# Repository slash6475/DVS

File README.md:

# DVS: Electronic Devil Stick
This project is an introduction to how to build quickly a native IP-based connected object on tiny platform. 
DVS is a simple electronic board composed of a 8 bits- microcontroller with Zigbee tranceiver, an accelerometer and some leds on child boards with an external button.
The software is implemented on Contiki OS, this micro-kernel dedicated to the Internet Of Thing allows 6LoWPAN networking (uIP stack with RPL for mesh network routing),
file system management to store data on flash or eeprom memories, shell interface over serial line, embedded webserver and more.

A simple Javascript page allows to design programs of RGB led sequences and to load them on the DVS platform over HTTP.
The programs are stored into the DVS file system and play on the leds according to the selected program by the external button.
In addition, the accelerometer and wireless communication can be used to control the leds. 
The wireless communication based on 6LoWPAN and HTTP can be operated by any other DVS platforms or computers.
Based on these features, a lot of scenarios and applications can be imagined. 

# Software
Contiki OS has a software architecture which facilitates the encapsulation of drivers and applications into independent containers.
Hence each component of DVS software is independent which facilitates implementation, modularity and code re-use.
Thanks to the shell over the serial line, it is possible to test the drivers of RGB leds and accelerometers, to manage the Webserver (start/stop) and the file system formating such as presented in following video.

## Shell Interface
Open the serial line over USB interface: 
```
minicom -D /dev/ttyUSB0 -b 19200
```
At booting time, different information on Contiki OS and DVS software configurations are provided such as networking, boot sequence, etc.
The command help provides the list of available commands:
```
neopixel test
neopixel ID_led R G B
mpu6050 start | stop
...
help
ps
kill
killall

```
## Programming
The software is implemented in C language and cross-platforms (MSP, AVR, ARM, X86, PIC, etc). The compilation must be executed in main project folder.
```
cd contiki-2.6/examples/dvs_main/
```
### Compilation
```
make all TARGET=avr-atmega128rfa1
avr-size --mcu=atmega128rfa1 dvs-main.avr-atmega128rfa1  -C
```

### Preparation
It is preferred to remove fuse and eeprom section to avoid to break fuse configuration and to erase programs stored in memories.
```
avr-objcopy -O ihex -R .eeprom -R .fuse -R .signature dvs-main.avr-atmega128rfa1 dvs-main.hex
```

### Loading
Example to load the program over ISP connector with a JTAG2 device.
```
sudo avrdude -p atmega128rfa1 -c jtag2isp -P usb -Uflash:w:dvs-main.hex
```
### 

## Arduino encapsulation
The DVS uses the accelerometer MPU6050 and the RGB leds Neopixel which have their librairy implemented in Arduino C++. 
Intead of implementing new librairies for Contiki OS, it is possible to link them dynamically at compilation step. 
Build a dvs.ino file with Arduino style and compile it, then remove the main.o and encapsulate it in a dynamic library.
More details in (contiki-2.6/apps/dvs)
```
avr-ar -cvq dvs_arduino.a *.o
```

In DVS Makefile of Contiki:
```
PROJECT_LIBRARIES=../../apps/dvs/libs/dvs_arduino.a
```

# Web Apps
The Web Interface is a simple javascript page which allows to generate and sequence chunk such as presented below. 
The number of program is not limited, however the sum of all sequences of all programs should be lower than file system size (4Kb).
Programs can be deleted individually, a long pressure on external button (> 20s) formats the file system.
```
OPERATION:TIME:RR1GG1BB1RR2GG2BB2 ...
add:0:001000000000000000000000ff0000ff0000000000000000000000000000000000000000ff0000ff0000000000000000000000
```

# Hardware

The master boards is composed of AVR Atmega128rfa1 with IEEE 802.15.4 radio transceiver, an accelerometer MPU6050 an an FTDI chipset for USB serial line. The external connectors provides pins to control Neopixel leds (16 in default child boards) and power stage of 4 AAAA batteries with their charger circuit based on LM317.
More detail and Eagle files in (/hardware).

## Scheme and PCB of Master Board

## Results

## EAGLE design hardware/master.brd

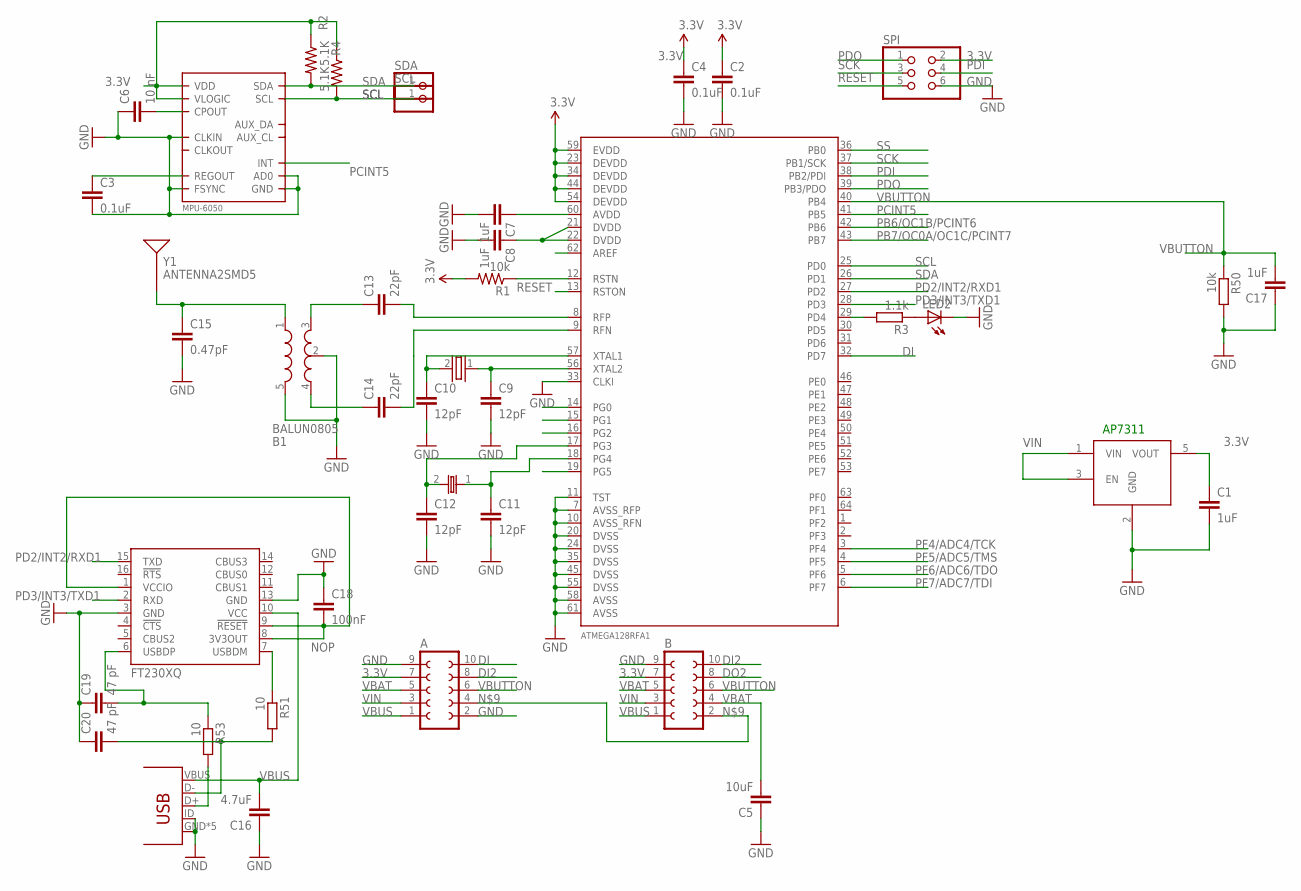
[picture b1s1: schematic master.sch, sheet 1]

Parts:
A: FE05-2W
B: FE05-2W
B1: BALUN0805; BALUN
C1: 1uF; C0603
C2, C3, C4: 0.1uF; 0603-CAP
C5: 10uF; 0603-CAP
C6: 10 nF; 0603-CAP
C7, C8, C17: 1uF; 0805
C9, C10, C11, C12: 12pF; 0603-CAP
C13, C14: 22pF; 0603-CAP
C15: 0.47pF; 0603-CAP
C16: 4.7uF; 0603-CAP
C18: 100nF; 0603-CAP
C19, C20: 47 pF; 0603-CAP
IC1: FT230XQ; QFN16
LED2: LEDCHIPLED_0603; CHIPLED_0603
MICRO-USB: USB-CONNECTOR; MICRO-USB-435-645
QUARTZ1: 753-7203
QUARTZ2: QUARTZ32768
R1: 10k; 0603-RES
R2, R4: 5.1K; 0603-RES
R3: 1.1k; R0603
R50: 10k; R0603
R51, R53: 10; R0603
SCL: PINHD-1X1; 1X01
SDA: PINHD-1X1; 1X01
SPI: PINHD-2X3; 2X03
U1: ATMEGA128RFA1; QFN-64
U$1: MPU-6050; QFN.24.4X4
U$7: MIC5366-2.8YMT; SOT23-5
Y1: ANTENNA2SMD5; ANTENNA-CHIP5

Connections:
3.3V: A.7, B.7, C1.1, C2.1, C4.1, R1.2, R2.1, R4.1, SPI.2, U1.23 (DEVDD), U1.34 (DEVDD), U1.44 (DEVDD), U1.54 (DEVDD), U1.59 (EVDD), U$1.8 (VLOGIC), U$1.13 (VDD), U$7.5 (VOUT)
AREF: U1.62 (AREF)
DI: A.10, U1.32 (PD7)
DI2: A.8, B.10
DO2: B.8
GND: A.2, A.9, B.9, B1.2 (GND), B1.5 (GND), C1.2, C2.2, C3.2, C4.2, C5.1, C6.1, C7.2, C8.2, C9.2, C10.2, C11.2, C12.2, C15.2, C16.1, C17.1, C18.1, C19.1, C20.1, IC1.3 (GND), IC1.13 (GND), LED2.C, MICRO-USB.GND, MICRO-USB.GND1 (GND), MICRO-USB.GND2 (GND), MICRO-USB.GND3 (GND), MICRO-USB.GND4 (GND), MICRO-USB.ID, R50.2, SPI.6, U1.7 (AVSS_RFP), U1.10 (AVSS_RFN), U1.11 (TST), U1.20 (DVSS), U1.24 (DVSS), U1.33 (CLKI), U1.35 (DVSS), U1.45 (DVSS), U1.55 (DVSS), U1.58 (AVSS), U1.61 (AVSS), U$1.1 (CLKIN), U$1.9 (AD0), U$1.11 (FSYNC), U$1.18 (GND), U$7.2 (GND)
unnamed: B1.3 (OUT1), C13.1
unnamed: B1.4 (OUT2), C14.1
unnamed: LED2.A, R3.1
unnamed: B1.1 (IN), C15.1, Y1.FEED
unnamed: C8.1, U1.21 (DVDD), U1.22 (DVDD)
unnamed: C14.2, U1.9 (RFN)
unnamed: C13.2, U1.8 (RFP)
unnamed: R3.2, U1.29 (PD4)
unnamed: A.4, B.2
unnamed: C7.1, U1.60 (AVDD)
unnamed: C3.1, U$1.10 (REGOUT)
unnamed: C10.1, QUARTZ1.2, U1.57 (XTAL1)
unnamed: C9.1, QUARTZ1.1, U1.56 (XTAL2)
unnamed: C12.1, QUARTZ2.2, U1.17 (PG3)
unnamed: C11.1, QUARTZ2.1, U1.18 (PG4)
unnamed: C6.2, U$1.20 (CPOUT)
unnamed: IC1.7 (USBDM), R51.1
unnamed: C20.2, MICRO-USB.D-, R51.2
unnamed: C19.2, IC1.6 (USBDP), R53.1
unnamed: MICRO-USB.D+, R53.2
NOP: C18.2, IC1.1 (VCCIO), IC1.8 (3V3OUT), IC1.9 (!RESET)
PB6/OC1B/PCINT6: U1.42 (PB6)
PB7/OC0A/OC1C/PCINT7: U1.43 (PB7)
PCINT5: U1.41 (PB5), U$1.12 (INT)
PD2/INT2/RXD1: IC1.15 (TXD), U1.27 (PD2)
PD3/INT3/TXD1: IC1.2 (RXD), U1.28 (PD3)
PDI: SPI.4, U1.38 (PB2/PDI)
PDO: SPI.1, U1.39 (PB3/PDO)
PF4/ADC4/TCK: U1.3 (PF4)
PF5/ADC5/TMS: U1.4 (PF5)
PF6/ADC6/TDO: U1.5 (PF6)
PF7/ADC7/TDI: U1.6 (PF7)
PG0: U1.14 (PG0)
PG1: U1.15 (PG1)
PG2: U1.16 (PG2)
PG5: U1.19 (PG5)
RESET: R1.1, SPI.5, U1.12 (RSTN)
RSTON: U1.13 (RSTON)
SCK: SPI.3, U1.37 (PB1/SCK)
SCL: R4.2, SCL.1, U1.25 (PD0), U$1.23 (SCL)
SDA: R2.2, SDA.1, U1.26 (PD1), U$1.24 (SDA)
SS: U1.36 (PB0)
VBAT: A.5, B.4, B.5, C5.2
VBUS: A.1, B.1, C16.2, IC1.10 (VCC), MICRO-USB.VBUS
VBUTTON: A.6, B.6, C17.2, R50.1, U1.40 (PB4)
VIN: A.3, B.3, U$7.1 (VIN), U$7.3 (EN)

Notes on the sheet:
AP7311

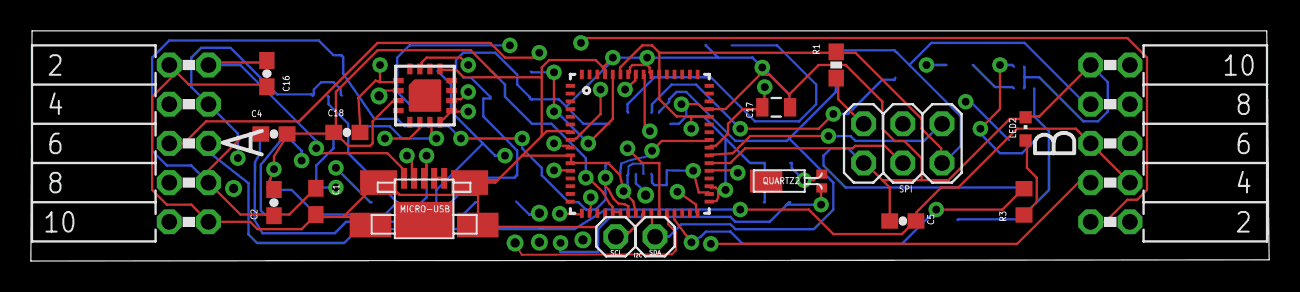
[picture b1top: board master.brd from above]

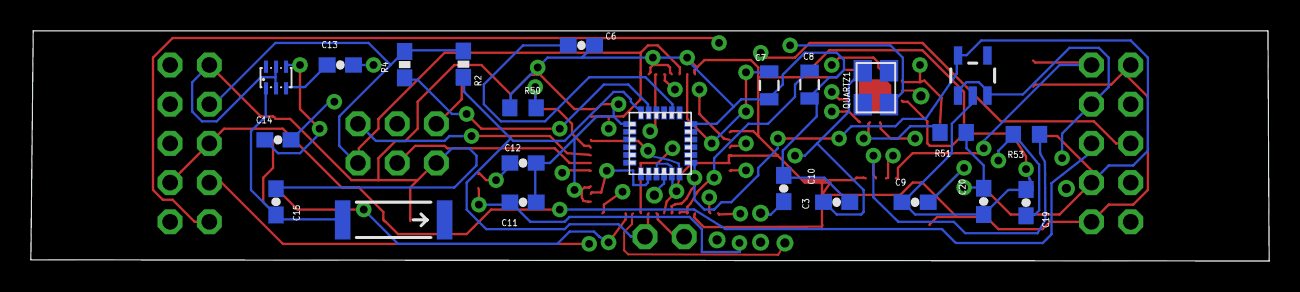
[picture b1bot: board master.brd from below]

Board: 4 copper layers, 80.2 x 14.9 mm, 42 parts (23 on the bottom side), 38 nets.

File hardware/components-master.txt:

Partlist

Exported from BatonDuDiable.brd at 02/02/2016 17:00:12

EAGLE Version 7.4.0 Copyright (c) 1988-2015 CadSoft

Assembly variant: 

Part      Value          Package           Library     Position (inch)       Orientation

A                        FE05-2W           con-lsta    (0.4 1.35)            R270
B                        FE05-2W           con-lsta    (2.75 1.35)           R90
B1        BALUN0805      BALUN             SparkFun    (2.45 1.5)            MR0
C1        1uF            C0603             rcl         (0.7 1.15)            R0
C2        0.1uF          0603-CAP          SparkFun    (0.7 1.25)            R0
C3        0.1uF          0603-CAP          SparkFun    (1.252 1.294)         MR90
C4        0.1uF          0603-CAP          SparkFun    (0.65 1.35)           R0
C5        10uF           0603-CAP          SparkFun    (1.95 1.25)           R270
C6        10 nF          0603-CAP          SparkFun    (1.672 1.575)         MR180
C7        1uF            0805              SparkFun    (1.25 1.5)            MR270
C8        1uF            0805              SparkFun    (1.15 1.5)            MR270
C9        12pF           0603-CAP          SparkFun    (0.9 1.2)             MR180
C10       12pF           0603-CAP          SparkFun    (1.1 1.2)             MR0
C11       12pF           0603-CAP          SparkFun    (1.9 1.2)             MR0
C12       12pF           0603-CAP          SparkFun    (1.9 1.3)             MR0
C13       22pF           0603-CAP          SparkFun    (2.3 1.5)             MR0
C14       22pF           0603-CAP          SparkFun    (2.45 1.35)           MR0
C15       0.47pF         0603-CAP          SparkFun    (2.45 1.2)            MR90
C16       4.7uF          0603-CAP          SparkFun    (0.85 1.5)            R90
C17       1uF            0805              SparkFun    (1.85 1.25)           R90
C18       0.1uF          0603-CAP          SparkFun    (0.8 1.35)            R0
C19       47 pF          0603-CAP          SparkFun    (0.7 1.25)            MR180
C20       47 pF          0603-CAP          SparkFun    (0.7 1.15)            MR180
IC1       FT230XQ        QFN16             ftdichip    (1 1.45)              R0
LED2                     CHIPLED_0603      led         (2.45 1.4)            R0
MICRO-USB USB-CONNECTOR  MICRO-USB-435-645 myrobotics2 (1 1.25)              R0
QUARTZ1   753-7203       753-7203          myrobotics2 (1 1.45)              MR90
QUARTZ2   QUARTZ32768    QUARTZ32768       myrobotics2 (1.9 1.4)             MR270
R1        10k            0603-RES          SparkFun    (2.05 1.5)            R180
R2        5.1K           0603-RES          SparkFun    (2.05 1.5)            MR270
R3        1.1k           R0603             rcl         (2.45 1.25)           R90
R4        5.1K           0603-RES          SparkFun    (2.15 1.5)            MR270
R50       10k            R0603             rcl         (1.85 1.45)           R90
R51       10             R0603             rcl         (0.8 1.35)            MR0
R53       10             R0603             rcl         (0.65 1.35)           MR0
SCL                      1X01              pinhead     (1.489 1.112)         R0
SDA                      1X01              pinhead     (1.589 1.112)         R0
SPI                      2X03              pinhead     (2.201 1.223)         R90
U$1       MPU-6050       QFN.24.4X4        MPU6050     (1.55 1.35)           MR0
U$7       MIC5366-2.8YMT SOT23-5           SparkFun    (0.7 1.5)             MR0
U1        ATMEGA128RFA1  QFN-64            SparkFun    (1.55 1.35)           R0
Y1        ANTENNA2SMD5   ANTENNA-CHIP5     SparkFun    (2.201 1.16)          MR0

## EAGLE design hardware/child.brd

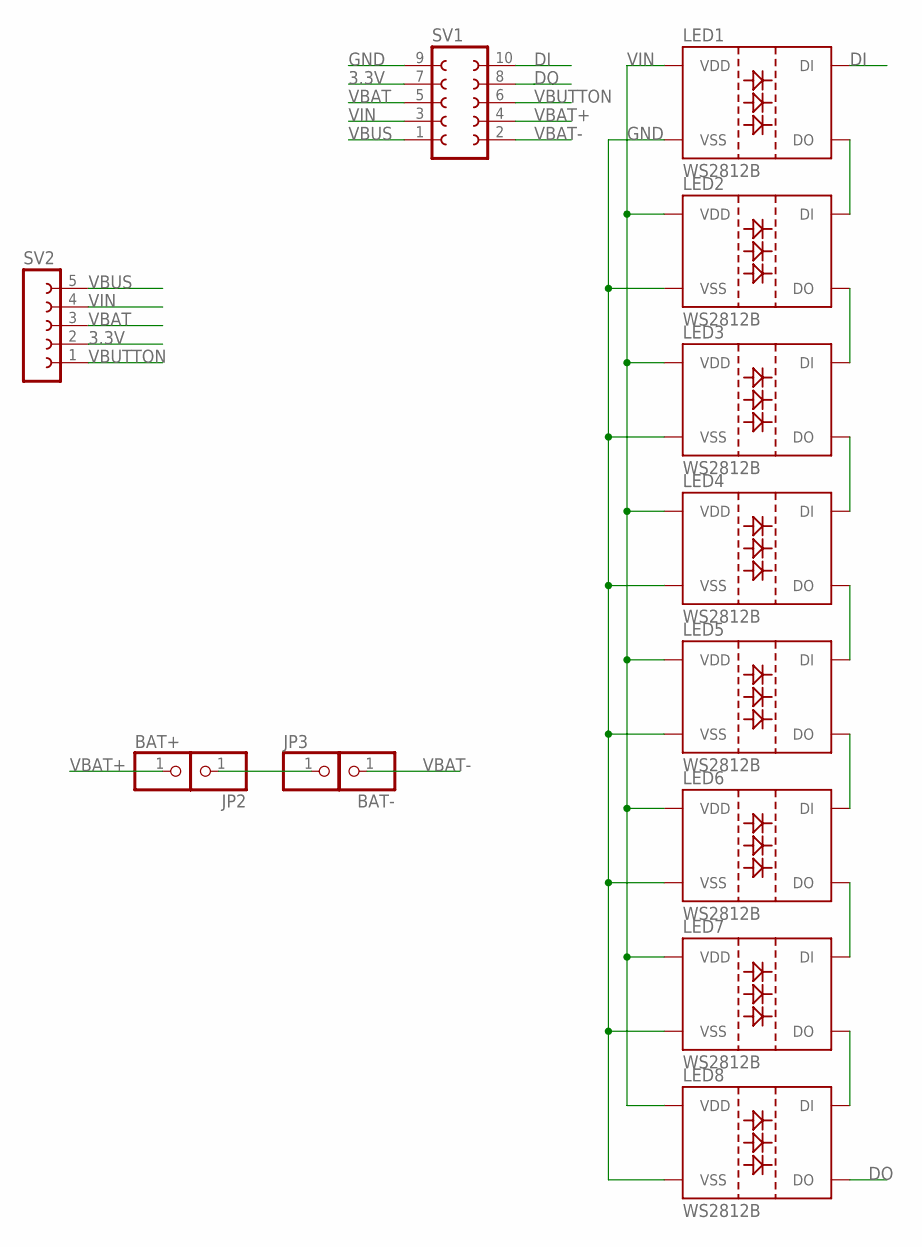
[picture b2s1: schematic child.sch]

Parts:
BAT+: PINHD-1X1; 1X01
BAT-: PINHD-1X1; 1X01
JP2, JP3: PINHD-1X1; 1X01
LED1, LED2, LED3, LED4, LED5, LED6, LED7, LED8: WS2812B
SV1: FE05-2W
SV2: FE05-1

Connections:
3.3V: SV1.7, SV2.2
DI: LED1.4 (DI), SV1.10
DO: LED8.2 (DO), SV1.8
GND: LED1.3 (VSS), LED2.3 (VSS), LED3.3 (VSS), LED4.3 (VSS), LED5.3 (VSS), LED6.3 (VSS), LED7.3 (VSS), LED8.3 (VSS), SV1.9
unnamed: LED1.2 (DO), LED2.4 (DI)
unnamed: LED2.2 (DO), LED3.4 (DI)
unnamed: LED3.2 (DO), LED4.4 (DI)
unnamed: LED4.2 (DO), LED5.4 (DI)
unnamed: LED5.2 (DO), LED6.4 (DI)
unnamed: LED6.2 (DO), LED7.4 (DI)
unnamed: LED7.2 (DO), LED8.4 (DI)
unnamed: JP2.1, JP3.1
VBAT: SV1.5, SV2.3
VBAT+: BAT+.1, SV1.4
VBAT-: BAT-.1, SV1.2
VBUS: SV1.1, SV2.5
VBUTTON: SV1.6, SV2.1
VIN: LED1.1 (VDD), LED2.1 (VDD), LED3.1 (VDD), LED4.1 (VDD), LED5.1 (VDD), LED6.1 (VDD), LED7.1 (VDD), LED8.1 (VDD), SV1.3, SV2.4

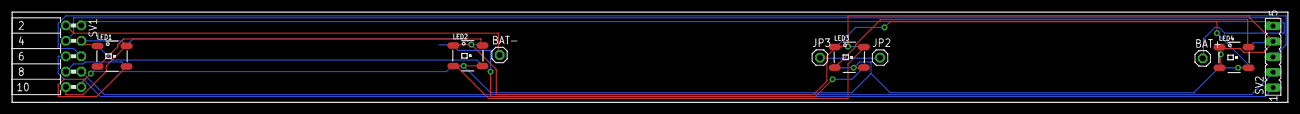
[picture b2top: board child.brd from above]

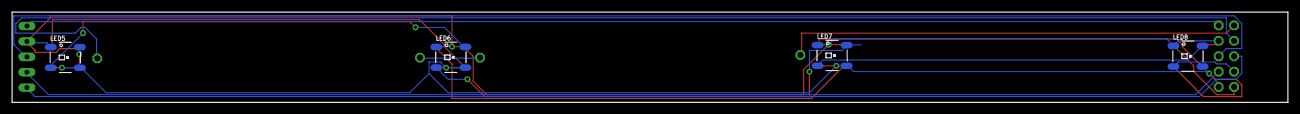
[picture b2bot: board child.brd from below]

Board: 4 copper layers, 210.8 x 14.9 mm, 14 parts (4 on the bottom side), 18 nets.

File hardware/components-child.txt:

Partlist

Exported from BatonDuDiable-leds.sch at 02/02/2016 17:00:40

EAGLE Version 7.4.0 Copyright (c) 1988-2015 CadSoft

Assembly variant: 

Part     Value          Device         Package         Library                    Sheet

BAT1                    BATTERYAAA-KIT BATTERY-AAA-KIT SparkFun-Electromechanical 1
BAT2                    BATTERYAAA-KIT BATTERY-AAA-KIT SparkFun-Electromechanical 1
LED1     WS2812B        WS2812B        WS2812B         WS2812                     1
LED2     WS2812B        WS2812B        WS2812B         WS2812                     1
LED3     WS2812B        WS2812B        WS2812B         WS2812                     1
LED4     WS2812B        WS2812B        WS2812B         WS2812                     1
LED5     WS2812B        WS2812B        WS2812B         WS2812                     1
LED6     WS2812B        WS2812B        WS2812B         WS2812                     1
LED7     WS2812B        WS2812B        WS2812B         WS2812                     1
LED8     WS2812B        WS2812B        WS2812B         WS2812                     1
SV1                     FE05-2W        FE05-2W         con-lsta                   1
SV2                     FE05-1         FE05-1          con-lsta                   1

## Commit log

2016-03-26 [IMPORT] DVS Software - v0.1
    Hardware: 8-Bit AVR Atmega128rfa1 IEEE 802.15.4
    Operating System
    * Contiki 2.6 / HTTP RestFul API / Coffee File System / Serial Shell / 6loWPAN (no RPL)
    * MPU6050 Accelerometer Arduino Driver embedded in Dynamic Library
    * Adafruit Neopixel Arduino Driver embedded in Dynamic Library
    Functionnalities:
2016-03-26 [BIN] Add binary file of compiled Arduino library * Neopixel Driver * MPU6050 Driver
2016-03-28 [NEW & FIX] Program 4 play leds according to accelerometer / Fix bug of interruptions between MPU6050 and external button
2016-03-28 [HARDWARE] Scheme, routing, component list and design rules
2016-03-28 [NEW] Add Web Controller (HTML/javascript page)
